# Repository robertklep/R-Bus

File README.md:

# R-Bus

Virtually every modern heater and thermostat will speak OpenTherm, but Remeha in their infinite wisdom created their own protocol called R-Bus. This protocol is to the best of my knowledge completely undocumented, so this is my attempt at doing that.

## Current status

### Mar 18, 2025

While I'm occupied launching a [local AI voice assistant](https://sanctuary-systems.com/sentinel-core/), someone emailed me [metadatapoints.xml](/metadatapoints.xml) that he extracted from Recom.
It appears to contain descriptions for all the registers, exciting!

### Dec 23, 2024

Ladies and gentelmen, we got him.

I updated the parser so I could live-stream data from the monitor board using

```bash
esphome logs --device rbus-monitor.local monitor.yaml | grep --line-buffered -oE "[0-9A-F]{2}(:[0-9A-F]{2})*$" | python parser.py --hex | tee unseen.txt
```

Then I updated the parser to keep track of seen messages and only print requests or replies with new data.
That cut a lot of noise, and let me see what's actually changing.

The most common message was the one Fried Microcrisps identified as a timestamp.
After a bit of messing around I was able to parse the timestamp and further cut the noise.

Then I was able to identify relevant messagest related to changing the operating mode and temperature.
And then I found a similar message that appears to be the current temperature!

So now we can parse
- the time (yay...)
- the active heater mode (scheduled, manual, off)
- the active hot water mode (scheduled, comfort, eco)
- the set temperature in tenths of degrees
- the current room temperature in hundres of degrees

That's all the basic info you'd want to monitor!

I've now moved on to further inspecting the cluster of FA register reads.
I'm fairly convinced all of them end with a 2 byte CRC of some sort, exact algorithm TBD.
It appears that the reply "unknown" bytes contain the length of the register and how many values?

I've written similar code to only print registers that have changed.
I've identified two registers that contain the hot water temperature setting in hundreths of degrees.
There seem to be a few registers that could plausably be water tempertures, but can't see those in the app to verify.

What I'd really like to find is the data for power usage.

These are some interesting registers:
```
542e01 (662,) (661,) # changes gradually
431f00 (4514,) (4484,) # changes gradually
540801 (0,) (3640,) # becomes zero if heating is turned off
500100 (1,) (0,) # hot water / heating?
```

### Dec 20, 2024

The monitor PCB arrived and works!
So now I have a permanent way to access logs from R-Bus. I just don't have somewhere to log to yet.

I found a RE discord:

> Fried Microcrisps
```
fa0001542e01 11ad 1a033701
```
> These to me look like
> 1 byte integer part <.> 3byte decimal part

```
fa0001302300 9e29 2c658403483aff71
```

> This I highlighted I think is most likely milliseconds
> Your time shown in screenshot is around 4.24pm or 1624H, for brevity it shall be 16.5 hours
> This is equal to 59400000 milliseconds, which in hex is 038A5F40 (be)
> Close enough
### Nov 27, 2024

A few realizations

The room temperature and water setpoint will be in a request (thermostat)
Outside temperature and water temperatures will be in replies (heat pump)

One request with a uint64 stands out to me:
```
Request flags=00000000 length=11 unknown=[F4 04 01] payload=34 23 01 00 00 00 00 00 00 4C 66
```

That's 19558 in decimal, possibly the room temperature in millidegrees?

In the ascii data we saw `Zone1`, and it made me realise that there can be multiple zones.
But also that the boiler is daisy chained behind the heat pump.
Could it be that some of those unknown triplets indicate the device and zone?

The `Zone1` messages appears to have a pretty regular structure, but it doesn't hold up with other messages
```
05 # number of fields
?? ?? typ  key?          len  data
01 01 [34] [10 01 00 00] [05] [43 48 00 00 00]
01 01 [34] [63 01 00 00] [01] [00]
01 01 [34] [0F 01 00 00] [14] [5A 6F 6E 65 31 00 00 00 00 00 00 00 00 00 00 00 00 00 00 00]
01 01 [34] [64 01 00 00] [04] [BF A9 00 00]
      typ  u16?
01 01 [5C] [18 44]
```

`EHC-07`:
```
09 # not a length
      tp key         ln dat
01 01 30 0F 00 00 00 14 45 48 43 2D 30 37 00 00 00 00 00 00 00 00 00 00 00 00 00 00
01 01 20 01 04 00 00 02 07 01
01 01 20 01 03 00 00 02 03 03
??
02 01 20 01 10 00 00 04 11 00 09 06
01 01 30 18 00 00 E6 ??
```
`7733242-06`:
```
02 0B 01 ???
#     tp key         ln data
01 01 20 01 0B 00 00 14 37 37 33 33 32 34 32 2D 30 36 00 00 00 00 00 00 00 00 00 00
01 01 50 3D 01 00 00 01 05
01 01 20 01 0A 00 00 04 61 01 0B 2E
01 01 20 01 02 00 00 02 07 02
13 ???
```
`MK2.1`:
```
no header
   ?? tp key         ln data
01 03 30 0F 00 00 00 14 4D 4B 32 2E 31 00 00 00 00 00 00 00 00 00 00 00 00 00 00 00
01 03 20 01 04 00 00 02 06 01
01 03 20 01 03 00 00 02 01 02
AD 09 ???
```
`7711844-06`:
```
      ln data
20 01 0B 37 37 31 31 38 34 34 2D 30 36 00
?? ?? ?? uint64?           "GO"?
00 00 00 00 00 00 00 00 00 47 4F
```

### Nov 25, 2024

I am trying to find the temperature in the data somewhere.
I've tried to parse every right-alligned number type that fits in a payload, and the most promising candidates
seem to be the numbers in the 20k range I saw last time, but they don't exactly match the temperature.

Could they be the water temperature?
You might expect hot water to be around 50&deg;C and the return temperature of the water to be slightly above ambient.
Sadly I can't see those temperatures in the app to verify.

Working on the assumption that in cases where the first 3 bytes of the request and reply payload match they indicate some register,
I wrote a script that groups messages by type and register to see how they change over time.
Many of them are constant and uninteresting, and som vary seemingly at random.
But some vary at a few distinct points in time, possibly in response to me messing with the settings.

I've collected these messages in [registers.txt](registers.txt).
For now they don't make much sense yet but it narrows down the search space.
It also clearly shows that there are some bit errors that could explain some weirdness.

I've also had the idea to look for ascii data in the payloads.
That wont get us the temperature, but it might give some other insights.
I've collected these messages in [ascii.txt](ascii.txt).
You can see fun stuff like `Zone1` for the heating zone, `EHC-07` the model of the heat pump, `7733242-06` and `7711844-06` could be serial numbers, and `MK2.1` could be a hardware revision, there are also heating modes like `Home` and `Sleep`. Other than that I'm not sure what we can learn here.

One thing it does seem to confirm is that the replies are coming from `EHC-07`, the heat pump,
which suggests the requests are from the thermostat.

This also suggests that we should look for the thermostat set points in the requests.

### Nov 22, 2024

I have started poking around with the message type.
I'm operating under the assumption that the first unknown byte is some kind of message type.
A particular interaction caught my eye where a `FA` request was answered with an `F3` reply.
In all `FA` requests there is a 5 byte payload that seems to be roughly

| byte | meaning |
|---|---|
|`20 02 01` | address?|
| `73 F0` | unknown |

and a `F3` reply of the form

| byte | meaning |
|---|---|
|`20 02 01` | same address |
| `00 00 00 00 00 00 6C 4A` | uint_64? |

I counted the reply bytes and their length and there seem to be 4 very common `Fx` replies with a common length. Most but not all follow the 3 byte "address" pattern.

```
Counter({'F7 7': 984,
         'F5 9': 802,
         'F8 6': 740,
         'F3 11': 715,
         'E6 24': 41,
         'FE 1': 17,
         'FA 5': 17,
         'E5 25': 14,
         'EF 15': 9,
         '00 0': 5,
         '2E 1': 3,
         '2D 1': 1,
         'F5 25': 1,
         '7D 9': 1,
         '2E 9': 1,
         '01 100': 1,
         'F9 5': 1,
         'F3 43': 1,
         '00 1': 1,
         '0A 1': 1,
         'A4 187': 1})
```

I tried parsing those supposed uint_64 with the following result. I was hoping it'd be something obvious like the temperature in millidegrees but while not miles off, not exactly. (recall it was 20&deg;C at the time)

```
(48, 35, 0, 12151716762370106083)
(32, 2, 1, 16762457204505351945)
(52, 33, 1, 25079)
(32, 2, 1, 16762457204505351945)
(32, 2, 1, 27722)
(48, 35, 0, 13315615791068642237)
(32, 2, 1, 16762457204505351945)
(32, 2, 1, 27722)
(52, 35, 1, 47222)
(52, 34, 1, 29879)
(52, 33, 1, 25079)
(32, 2, 1, 16762457204505351945)
(32, 2, 1, 27722)
(48, 35, 0, 10876635117870837854)
(32, 2, 1, 27722)
(52, 35, 1, 47222)
(52, 34, 1, 29879)
(52, 33, 1, 25079)
(48, 35, 0, 3173792004718625437)
(32, 2, 1, 16762457204505351945)
(32, 2, 1, 27722)
```

One thing that is slightly concerning is that there are some parse errors after really long messages. Not sure if just a glitch in the serial data, or something funky like replacing certain bytes. I remember Pokemon has a whole thing where they replace 0xFE with something else and then send a whole mask array, because 0xFE is their handshake byte.

### Nov 8, 2024

I have started building a parser that breaks a stream of bytes from the logger into messages.
Turns out I was decoding the bit order wrong, and now some things are more obvious.
The format seems to be

| byte | meaning |
|---|---|
|`01 00`| header |
| `01` | request/reply |
| `00` | some bit flags? |
| `07` | payload length |
| `F7 01 FE` | unknown |
| `10 03 01 FF FF 85 9C` | payload |

### Nov 6, 2024

I have built a data logger with a comparator and an Arduino, and collected a good long chunk of messages in [log.txt](log.txt),
while simultaneously collecting screenshots of the official app in [screenshots](screenshots) and adjusting the temperature between 20&deg;C and 22&deg;C.

The schematic of the datalogger is in [demodulator.pdf](demodulator.pdf), and the Arduino sketch is in [echo.ino](echo/echo.ino).

Analysis of the new data tbd.

### Oct 14, 2024

I have collected an oscilloscope capture of the wires between my [Remeha Elga Ace](https://www.remeha.nl/product/elga-ace) heat pump and [Remeha eTwist](https://www.remeha.nl/product/etwist) thermostat. This can be found as a compressed CSV file in `RigolDS1.tar.xz`.

It appears to be a simple on-off keying scheme with a 500kHz carrier and a 10kHz bit rate.

To decode the capture, I first demodulate it with `demodulate.py`, and then import `demodulated_output.csv` in [urh](https://github.com/jopohl/urh). Automated detection worked correctly, but I did set the pause threshold and message length divisor to 10. The analysis tab proved unhelpful so I just exported the data to `protocol.proto.xml`.

My hunch is that it's regular old 8N1 UART data, but possibly inverted. In `decode_bytes.py` I read the exported XML from urh, verify start and stop bits, and extract the data bits. The output is stored in `messages.txt`, a sample is provided below:

```
80 00 00 00 A0 5F 00 80 2C C4 80 F9 95
80 00 80 00 D0 CF 80 7F 2C C4 80 00 00 00 00 00 00 1D 6E
80 00 00 00 A0 5F 00 80 2C 44 80 F0 15
80 00 80 00 D0 CF 80 7F 2C 44 80 00 00 00 00 00 00 2E ED
```

If you look at the raw capture you can see two slightly different magnitudes, so I think it is reasonable to assume this are the two devices in a request/response interaction. It seems like the first bytes are just some kind of addressing or synchronization, with the third byte being `00` in the request and `80` in the response. Possibly the fifth byte could be some message ID.

In some of the messages the last 8 bytes look like it could be an uint64 (`00 00 00 00 00 00 2E ED`), hopefully representing some useful value. The request has two bytes in that place. (`F9 95`) The three bytes before that match in the request and reply, and the byte before that is off by one. (`80 2C 44 80` -> `7F 2C 44 80`) Maybe there is some register ID or message sequence number in there?

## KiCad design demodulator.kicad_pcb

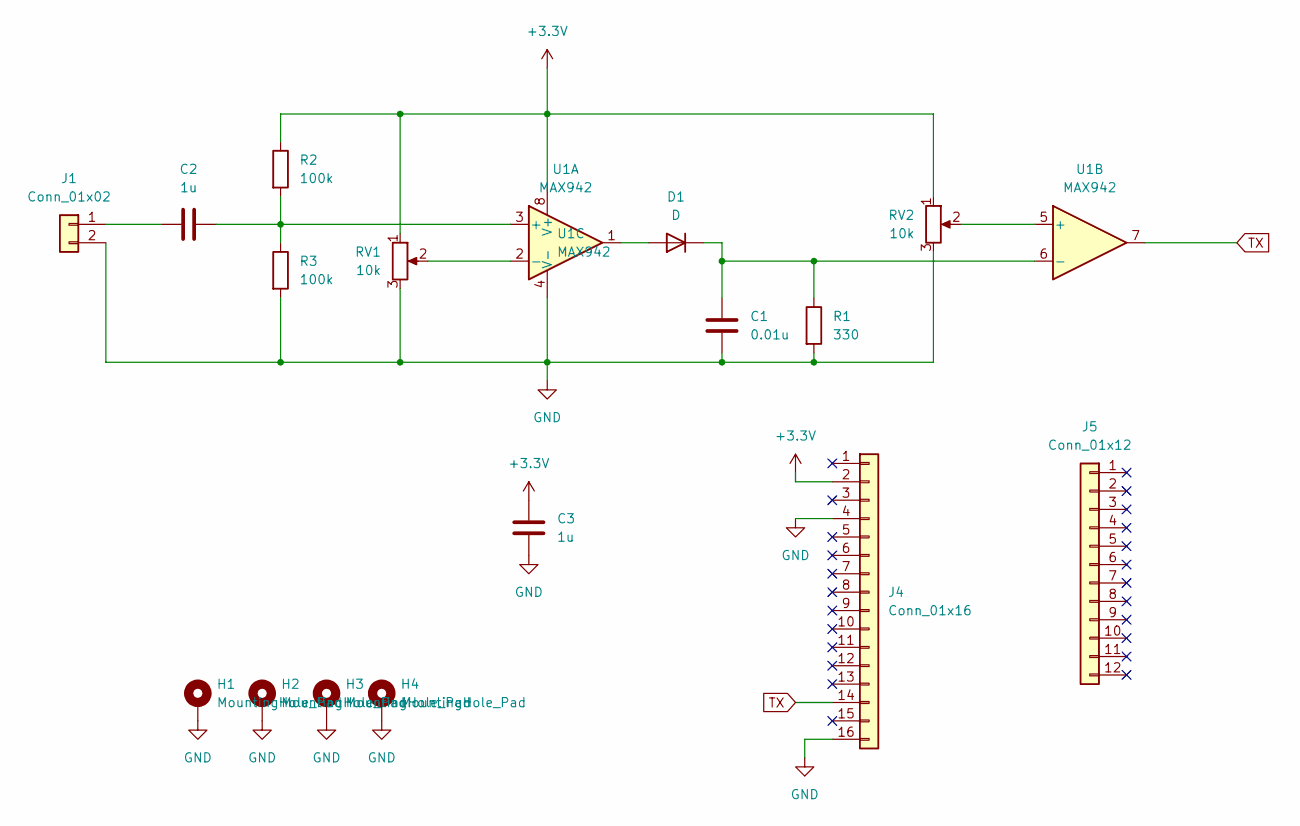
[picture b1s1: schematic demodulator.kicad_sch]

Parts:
C1: 0.01u; C_0805_2012Metric_Pad1.18x1.45mm_HandSolder
C2, C3: 1u; C_0805_2012Metric_Pad1.18x1.45mm_HandSolder
D1: D; D_0805_2012Metric_Pad1.15x1.40mm_HandSolder
H1, H2, H3, H4: MountingHole_Pad; MountingHole_2.2mm_M2_ISO14580_Pad
J1: Conn_01x02; Samtec_HPM-02-05-x-S_Straight_1x02_Pitch5.08mm
J4: Conn_01x16; PinSocket_1x16_P2.54mm_Vertical
J5: Conn_01x12; PinSocket_1x12_P2.54mm_Vertical
R1: 330; R_0805_2012Metric_Pad1.20x1.40mm_HandSolder
R2, R3: 100k; R_0805_2012Metric_Pad1.20x1.40mm_HandSolder
RV1, RV2: 10k; Potentiometer_Bourns_TC33X_Vertical
U1: MAX942; SOIC-8_3.9x4.9mm_P1.27mm

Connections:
+3.3V: C3.2, J4.2, R2.1, RV1.1, RV2.1, U1.8 (V+)
GND: C1.2, C3.1, H1.1, H2.1, H3.1, H4.1, J1.2, J4.4, J4.16, R1.2, R3.2, RV1.3, RV2.3, U1.4 (V-)
unnamed: D1.2 (A), U1.1
unnamed: C1.1, D1.1 (K), R1.1, U1.6 (-)
unnamed: C2.1, J1.1
unnamed: C2.2, R2.2, R3.1, U1.3 (+)
unnamed: RV1.2, U1.2 (-)
unnamed: RV2.2, U1.5 (+)
TX: J4.14, U1.7

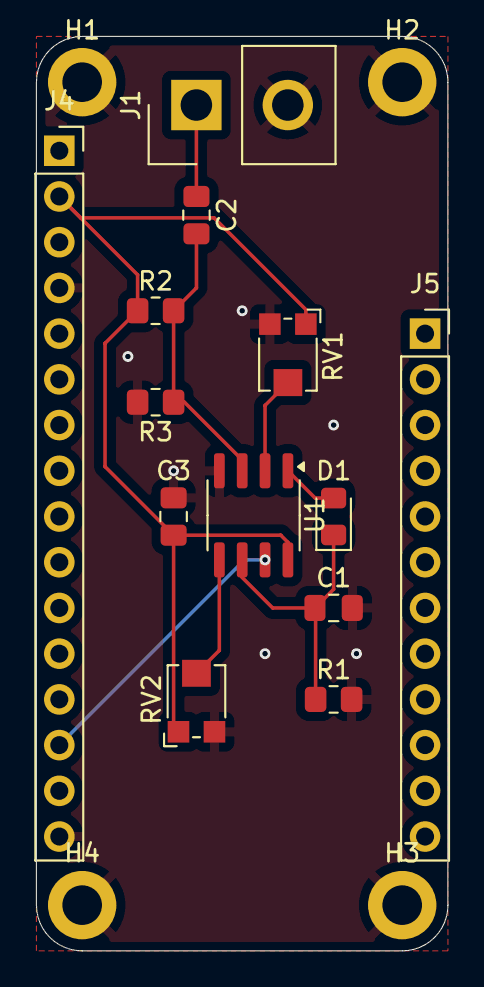
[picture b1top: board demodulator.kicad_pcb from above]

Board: 2 copper layers, 22.9 x 50.8 mm, 17 parts (0 on the bottom side), 9 nets.

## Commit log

2024-10-14 Create LICENSE
2024-10-14 add code and data
2024-10-14 document progress
2024-10-14 add protocol file
2024-10-14 adition
2024-10-14 speculation
2024-11-06 add data log and app screenshots
2024-11-06 describe and document progress
2024-11-06 unfk the formatting
2024-11-06 typo
2024-11-08 add partial parser, thanks claude
2024-11-22 today's updates
2024-11-25 nov 25 updates
2024-11-25 add ascii data
2024-11-26 add extra note
2024-11-27 5/10 many notes
2024-11-29 PCB design
2024-12-20 add esphome yaml
2024-12-23 parse temperature and stuff
2025-01-05 add more correctly decoded logging data
2025-03-18 Add xml file
2025-04-13 Added new parser (WIP) based on object dictionary(-ish)
2025-04-13 Don't symlink od.json
2025-04-13 Parse array-type datapoints correctly, renamed `od` to `datapoints`
2025-04-15 Implemented checksum validation, visible string support, various small changes
